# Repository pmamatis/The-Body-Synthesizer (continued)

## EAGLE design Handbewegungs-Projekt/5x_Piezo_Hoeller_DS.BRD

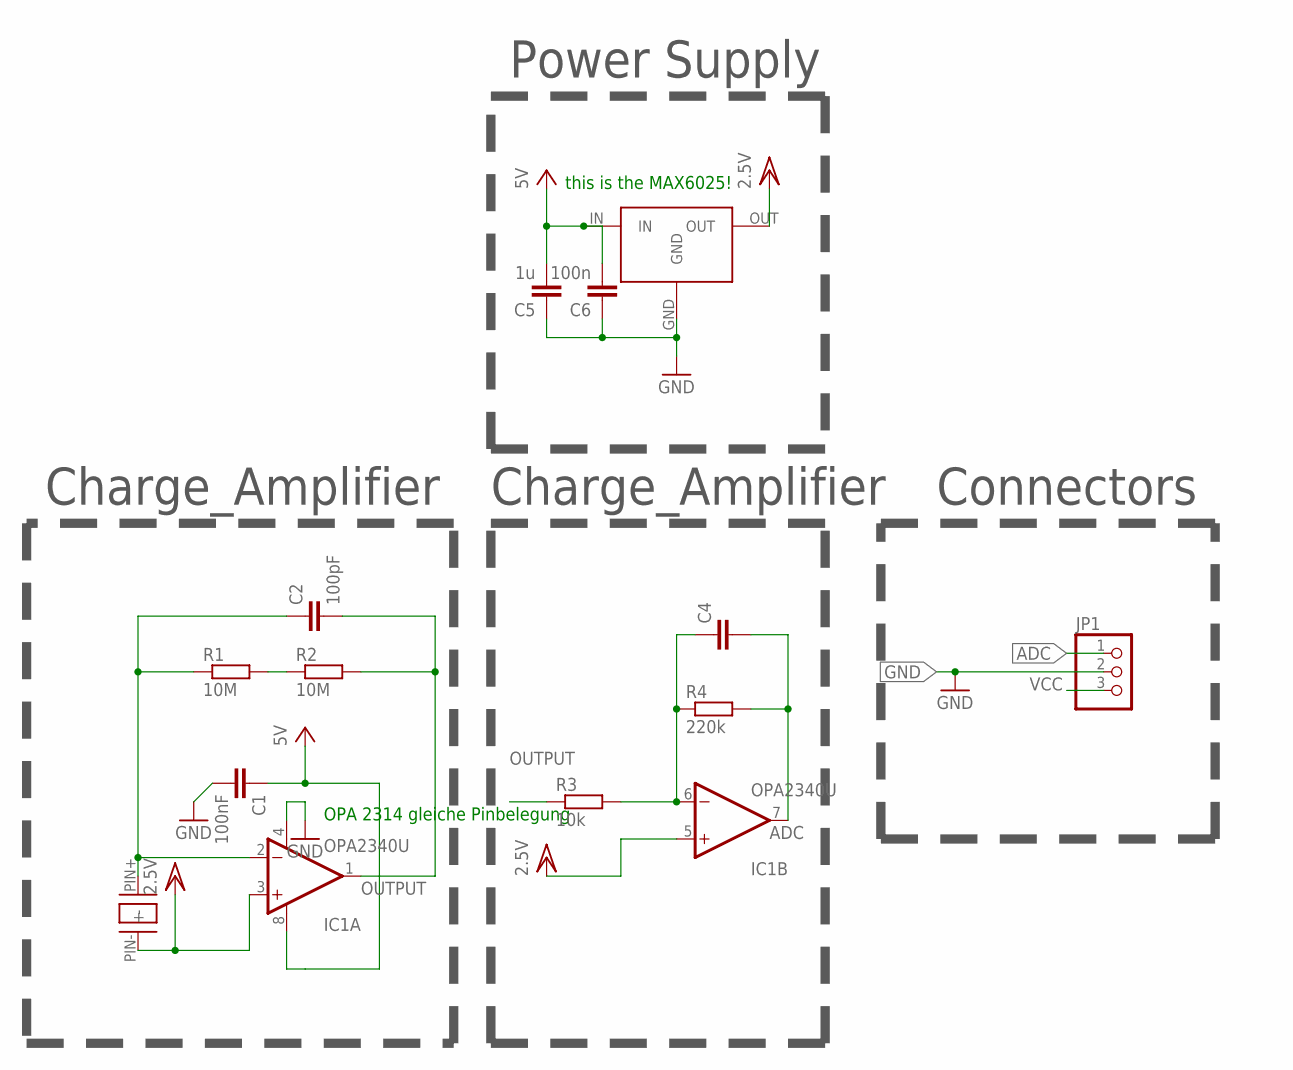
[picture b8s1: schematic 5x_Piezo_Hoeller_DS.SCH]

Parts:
C1: 100nF; C0603
C2: 100pF; C0603
C4: C-EUC0603; C0603
C5: 1u; C0603
C6: 100n; C0603
IC1: OPA2340U; SO08
JP1: PINHD-1X3; 1X03
R1, R2: 10M; R0603
R3: 10k; R0603
R4: 220k; R0603
U$1: MAX6018X; SOT-3
U$2: 10MMSCHEIBE; 10MM_SCHEIBE

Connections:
ADC: C4.2, IC1.7 (OUT), JP1.1, R4.2
GND: C1.2, C5.1, C6.1, IC1.4 (V-), JP1.2, U$1.GND
unnamed: C2.1, IC1.2 (-IN), R1.1, U$2.PIN+ (+)
unnamed: R1.2, R2.1
unnamed: C4.1, IC1.6 (-IN), R3.2, R4.1
OUTPUT: C2.2, IC1.1 (OUT), R2.2, R3.1
VCC: C1.1, C5.2, C6.2, IC1.8 (V+), JP1.3, U$1.IN
VCC/2: IC1.3 (+IN), IC1.5 (+IN), U$1.OUT, U$2.PIN- (-)

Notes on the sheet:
Power Supply
Charge_Amplifier
Connectors
OPA 2314 gleiche Pinbelegung
this is the MAX6025!

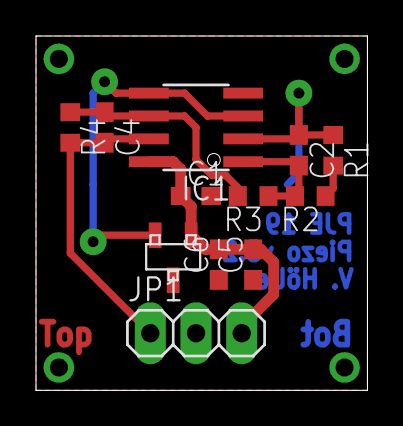
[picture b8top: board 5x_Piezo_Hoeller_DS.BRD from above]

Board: 2 copper layers, 18.4 x 19.7 mm, 13 parts (1 on the bottom side), 8 nets.

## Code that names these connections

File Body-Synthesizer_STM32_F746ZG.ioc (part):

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Mcu.Name=STM32F746ZGTx
Mcu.Package=LQFP144
Mcu.UserName=STM32F746ZGTx
PA0/WKUP.GPIOParameters=GPIO_Label
PA0/WKUP.GPIO_Label=DISP_DC
PA0/WKUP.Signal=GPIO_Output
PA2.Signal=USART2_TX
PA4.Signal=COMP_DAC1_group
PA5.Signal=COMP_DAC2_group
PA6.GPIOParameters=GPIO_Label
PA6.GPIO_Label=VRx
PA6.Signal=ADCx_IN6
PB0.GPIOParameters=GPIO_Label
PB0.GPIO_Label=VRy
PB0.Signal=ADCx_IN8
PB1.GPIOParameters=GPIO_Label
PB1.GPIO_Label=DISP_BUSY
PB1.Signal=GPIO_Input
PB14.GPIOParameters=GPIO_Label
PB14.GPIO_Label=Red_User_LED
PB14.Signal=GPIO_Output
PB2.GPIOParameters=GPIO_Label
PB2.GPIO_Label=SD_DI_MOSI
PB2.Mode=Full_Duplex_Master
PB2.Signal=SPI3_MOSI
PB3.GPIOParameters=GPIO_Label
PB3.GPIO_Label=DISP_CLK
PB3.Mode=Full_Duplex_Master
PB3.Signal=SPI1_SCK
PB4.Mode=Full_Duplex_Master
PB4.Signal=SPI1_MISO
PB5.GPIOParameters=GPIO_Label
PB5.GPIO_Label=DISP_DIN
PB5.Mode=Full_Duplex_Master
PB5.Signal=SPI1_MOSI
PB7.GPIOParameters=GPIO_Label
PB7.GPIO_Label=Blue_User_LED
PB7.Signal=GPIO_Output
PC0.GPIOParameters=GPIO_Label
PC0.GPIO_Label=Poti
PC0.Signal=ADCx_IN10
PC10.GPIOParameters=GPIO_Label
PC10.GPIO_Label=SD_CLK
PC10.Mode=Full_Duplex_Master
PC10.Signal=SPI3_SCK
PC11.GPIOParameters=GPIO_Label
PC11.GPIO_Label=SD_DO_MISO
PC11.Mode=Full_Duplex_Master
PC11.Signal=SPI3_MISO
PC13.GPIOParameters=GPIO_Label
PC13.GPIO_Label=ENTER_USER
PC13.Signal=GPXTI13
PC2.GPIOParameters=GPIO_Label
PC2.GPIO_Label=KEYBOARD_ADC
PC2.Signal=ADCx_IN12
PC3.Signal=ADCx_IN13
PC8.GPIOParameters=GPIO_Label,GPIO_ModeDefaultOutputPP
PC8.GPIO_Label=DISP_CS
PC8.GPIO_ModeDefaultOutputPP=GPIO_MODE_OUTPUT_PP
PC8.Signal=GPIO_Output
PC9.GPIOParameters=GPIO_Label
PC9.GPIO_Label=BACK
PC9.Signal=GPXTI9
PD6.Signal=USART2_RX
PD8.Mode=Asynchronous
PD8.Signal=USART3_TX
PD9.Mode=Asynchronous
PD9.Signal=USART3_RX
PE2.GPIOParameters=GPIO_Label
PE2.GPIO_Label=F4_SPI_CLK
PE2.Mode=Full_Duplex_Master
PE2.Signal=SPI4_SCK
PE5.GPIOParameters=GPIO_Label
PE5.GPIO_Label=F4_SPI_MISO
PE5.Mode=Full_Duplex_Master
PE5.Signal=SPI4_MISO
PE6.GPIOParameters=GPIO_Label
PE6.GPIO_Label=F4_SPI_MOSI
PE6.Mode=Full_Duplex_Master
PE6.Signal=SPI4_MOSI
PE8.GPIOParameters=GPIO_Label
PE8.GPIO_Label=ENTER
PE8.Signal=GPXTI8
PF0.GPIOParameters=GPIO_Label
PF0.GPIO_Label=GYRO_I2C_SDA
PF0.Mode=I2C
PF0.Signal=I2C2_SDA
PF1.GPIOParameters=GPIO_Label
PF1.GPIO_Label=GYRO_I2C_SCL
PF1.Mode=I2C
PF1.Signal=I2C2_SCL
PF10.GPIOParameters=GPIO_Label
PF10.GPIO_Label=SD_CS
PF10.Signal=GPIO_Output
PF12.GPIOParameters=GPIO_Label
PF12.GPIO_Label=DISP_RST
PF12.Signal=GPIO_Output
PF3.Mode=IN9
PF3.Signal=ADC3_IN9
PF5.Mode=IN15
PF5.Signal=ADC3_IN15
PF6.GPIOParameters=GPIO_Label
PF6.GPIO_Label=ADC_EMG_DC
PF6.Mode=IN4
PF6.Signal=ADC3_IN4
PF7.GPIOParameters=GPIO_Label
PF7.GPIO_Label=ADC_EMG_AC
PF7.Mode=IN5
PF7.Signal=ADC3_IN5
PG0.GPIOParameters=GPIO_Label,GPIO_ModeDefaultEXTI
PG0.GPIO_Label=SW
PG0.GPIO_ModeDefaultEXTI=GPIO_MODE_IT_FALLING
PG0.Signal=GPXTI0
PH0/OSC_IN.Mode=HSE-External-Oscillator
PH0/OSC_IN.Signal=RCC_OSC_IN
PH1/OSC_OUT.Mode=HSE-External-Oscillator
PH1/OSC_OUT.Signal=RCC_OSC_OUT
RCC.HSE_VALUE=8000000
RCC.SYSCLKFreq_VALUE=216000000
RCC.SYSCLKSource=RCC_SYSCLKSOURCE_PLLCLK
board=custom

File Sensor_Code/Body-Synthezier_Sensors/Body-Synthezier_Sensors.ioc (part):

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Mcu.Name=STM32F446R(C-E)Tx
Mcu.Package=LQFP64
Mcu.UserName=STM32F446RETx
PA10.GPIOParameters=GPIO_Label
PA10.GPIO_Label=LED_STRONG_TILT_BACK
PA10.Signal=GPIO_Output
PA13.GPIOParameters=GPIO_Label
PA13.GPIO_Label=TMS
PA13.Signal=SYS_JTMS-SWDIO
PA14.GPIOParameters=GPIO_Label
PA14.GPIO_Label=TCK
PA14.Signal=SYS_JTCK-SWCLK
PA2.GPIOParameters=GPIO_Label
PA2.GPIO_Label=USART_TX
PA2.Mode=Asynchronous
PA2.Signal=USART2_TX
PA3.GPIOParameters=GPIO_Label
PA3.GPIO_Label=USART_RX
PA3.Mode=Asynchronous
PA3.Signal=USART2_RX
PA5.Mode=Full_Duplex_Slave
PA5.Signal=SPI1_SCK
PA6.Mode=Full_Duplex_Slave
PA6.Signal=SPI1_MISO
PA7.Mode=Full_Duplex_Slave
PA7.Signal=SPI1_MOSI
PA8.GPIOParameters=GPIO_Label
PA8.GPIO_Label=LED_TILT_FRONT
PA8.Signal=GPIO_Output
PB10.GPIOParameters=GPIO_Label
PB10.GPIO_Label=LED_STRONG_TILT_FRONT
PB10.Signal=GPIO_Output
PB13.GPIOParameters=GPIO_Label
PB13.GPIO_Label=LED_STRONG_TILT_RIGHT
PB13.Signal=GPIO_Output
PB14.GPIOParameters=GPIO_Label
PB14.GPIO_Label=LED_CALIBRATED
PB14.Signal=GPIO_Output
PB3.GPIOParameters=GPIO_Label
PB3.GPIO_Label=LED_TILT_BACK
PB3.Signal=GPIO_Output
PB4.GPIOParameters=GPIO_Label
PB4.GPIO_Label=LED_STRONG_TILT_LEFT
PB4.Signal=GPIO_Output
PB5.GPIOParameters=GPIO_Label
PB5.GPIO_Label=LED_TILT_LEFT
PB5.Signal=GPIO_Output
PB8.Mode=I2C
PB8.Signal=I2C1_SCL
PB9.Mode=I2C
PB9.Signal=I2C1_SDA
PC13.GPIOParameters=GPIO_Label,GPIO_ModeDefaultEXTI
PC13.GPIO_Label=B1 [Blue PushButton]
PC13.GPIO_ModeDefaultEXTI=GPIO_MODE_IT_FALLING
PC13.Signal=GPXTI13
PC14-OSC32_IN.Signal=RCC_OSC32_IN
PC15-OSC32_OUT.Signal=RCC_OSC32_OUT
PC4.GPIOParameters=GPIO_Label
PC4.GPIO_Label=LED_TILT_RIGHT
PC4.Signal=GPIO_Output
PC9.GPIOParameters=GPIO_Label
PC9.GPIO_Label=MPU6050_Power
PC9.Signal=GPIO_Output
PH0-OSC_IN.Signal=RCC_OSC_IN
PH1-OSC_OUT.Signal=RCC_OSC_OUT
RCC.HSE_VALUE=8000000
RCC.SYSCLKFreq_VALUE=84000000
RCC.SYSCLKSource=RCC_SYSCLKSOURCE_PLLCLK
board=NUCLEO-F446RE
boardIOC=true

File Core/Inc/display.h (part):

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} y_row_value;

typedef enum {
	STEP1 = 40,
	STEP2 = 60,
	STEP3 = 80,
	STEP4 = 100,
	STEP5 = 120,
	STEP6 = 140,
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
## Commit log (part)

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2020-06-24 all_sines_LUT.m added
2020-06-24 cosmetics
2020-06-24 1.4 in progress
2020-06-24 dlmwrite
2020-06-30 LUT code writer 1.0
2020-06-30 sinLLUT
2020-07-02 verbessert
    LFO geht nicht
2020-07-07 BLOCKSIZE = 24k, wegen RAM speicher
    LUT und LFO im Flash gespeichert
2020-07-07 LFO calculate verbessert
    LUT und LFo in Flash schreiben hinzugefügt
2020-07-08 LFO Periode/4
2020-07-08 Samplerate = 96k
2020-07-08 Picture added
2020-07-30 Signal Syntrhesis 1.4 works first atempt, no bugs found but also not searched
2020-08-04 Signalsyntheses, möglicherweise fertig?!
2020-08-06 dynamische Voice Lautstärke
2020-08-12 changed LFO precision from 2 to 5
2020-08-12 LFO ready to use
2020-08-12 filters merged with new signal synthesis, LP test successful
2020-09-28 less RAM usage
    calculate_vector isnow directly given to the DAC, without having the output_vector
2020-09-30 Tremolo works, but still have to clean up!
2020-09-30 Tremolo is implemented!
2021-01-21 organized the code for the distortion-effect
2021-03-04 Add new directory by wiselom
2021-04-25 EMG board updates
2021-04-25 BSB.graphml added
2021-04-25 Lowpass filter working still! Next up: try band/highpass
2021-05-02 added Together Branch, merged tremolo and filters
2021-05-07 debug session
2021-05-07 debug session gelöst
2021-05-07 nichts hat sich veränder "nochmal pushen"
2021-05-14 merging begins
2021-05-14 Master -Branch First Commit
    This Branch must contain only working states of the Software. Use this Branch to develop and then merge back if everything is functional
2021-05-16 Parallel processing implemented: works for 1 band already, next up: Test all bands at the same time
2021-05-16 All bands tested at the same time with several test tones, worked! Next up: have a look to amplitude levels (e.g. testing filters with white noise)
2021-05-19 define aquidistance and atan_LUT_y in distortion-files instead of main-files
2021-05-21 added soft clipping based on exponential function;
    added CMSIS-DSP and CMSIS-Core-Library
2021-05-21 EQ Bandpass debugged, Band 1 & 2 working properly - Next up: Test Band 3 - 5
2021-05-23 Individual Bandpass filters implemented, center frequencies have to be specified
2021-05-23 started with the new structure, which should be implemented
2021-05-25 now it is possible to turn Voice1 Off and On again
2021-05-26 Switching between Voices, ADSR, EQ, Distortion and Tremolo possible
2021-05-27 Code angepasst
2021-06-01 Keyboard slightly edited (2 drills) for manufacturing
2021-06-01 ADC reads AC (in12) and DC (in13) channel of emg
2021-06-02 All types of filter implemented, next up: test new ones with poti (change cutoff, Q, Gain)
2021-06-02 Warnings solved, now Signal_Syntheis Errors occured >> Will be fixed by Paul and Marc
2021-06-02 Keyboard panelized
2021-06-02 emg adc ready to use
2021-06-06 ADC1 Channel 13 read in for poti value while signal synthesis as well as printing via uart is working
2021-06-06 Debugging necessary
2021-06-07 Tremolo does not work in combination with display; permanent calculation of LFO could be the problem
2021-06-08 Voice, Distortion and Tremolo work together; had to remove effects_process and put function calls into signal_synthesis
2021-06-11 HS / LS tested successfully with changing Gain & Cutoff in Filters_Reinit() - next up: PEQ
2021-06-11 PEQ Att. Problem solved by introducing Notch filter >> Complete EQ works now!
2021-06-13 Mainboard created
2021-06-13 pinbelegung für display geändert (SPI)
2021-06-18 changed CLK and MOSI from SPI6 to SPI1 for the display
2021-06-18 changed Button_Back and DISP_CS pins
2021-06-21 Pinout test done, SD card works in this setup!
2021-06-21 update rotation of the display
2021-06-22 integrated keyboardmode on/off, bu adsr reacts too slow. processing has to be done at different place
2021-06-22 Auf dem stand von Keyboard-Branch, ADSR weißt dennoch Fehler auf
2021-06-24 Optimized for speed, keyboard can be played now
2021-06-25 ADSR works in combination with the display! Now its possible to switch between keyboard- and synthesizemode and play with the parameters
2021-06-27 soft clipping added, but amplitude does change when gain is increased
2021-06-28 Bemaßung hinzugefügt
2021-07-10 Mainboard updated II
2021-07-15 Mainboard updated IV
2021-07-18 Mainboard updated VI (ready2route)
2021-07-18 Mainboard updated VIII: routed completely, only need to check SD Card size
2021-07-20 Production data for ordering Mainboard, Keys, UI and EQ at JLCPCB
2021-07-21 Production data changed
2021-07-22 Display-Update stört Signale nicht mehr so stark, da nun seltener geupdated wird
2021-08-12 Namen zurechtgerückt
2021-08-12 Display structure changed
2021-08-13 new basic structure implemented
2021-08-13 EQ BOM updated
2021-08-15 BOM updated
2021-08-15 added input_interfaces files
2021-08-19 deleted HAL_ADC_Start_DMA(&hadc1, &Display.ADC1input, 1); in main.c file
2021-08-23 added Interface Controll
2021-08-23 p_Equalizer_Settings implemented and now ready to merge with p_Equalizer_Overview
2021-08-23 p_Equalizer_overview and p_Equalizer_Settings combined
2021-08-24 cleaned up code
2021-08-24 Voices page is working
2021-08-25 Peak detection implemented, not properly working with LED
2021-08-31 EKG Recognition working!!!
2021-09-02 Added pictures for EMG and Mainboard for final report
2021-09-03 display structure is running correctly, but filter page is buggy, when filter is turned on
2021-09-03 drum computer works! now lookup tables have to be read in via sd card
2021-09-03 fixed some display-bugs and dummy structure has to be implemented
2021-09-04 Single Output already possible
2021-09-04 Drumsaples added, reading from SD card works, only need to find a solution for puting LUTs into FLASH and not RAM
2021-09-05 Tried to stream samplewise from SD Card, implicit Bug because of missing header?
2021-09-09 Drum_Computer now working with 4 Samples at a time, loading them from SD card into RAM. Drumsamples are sampled down by 4
2021-09-09 Poti & Filters included to have a lowshelf filter on drums with settable cutoff
2021-09-10 Test
2021-09-10 invert/toggle DrumMatrix entrys in GPIO external interrupt Callback; next filled rectangle should be set/reset
2021-09-10 LFO uncommented
2021-09-10 Drums working together with NewSignal and partly with Filtercutoff reinit. SR: 48kHz, sinLUTs and wavLUTs adapted via matlab scripts. Next up: Trying bigger blocksizes or even lower SR?
2021-09-10 48 kHz change
2021-09-10 9 voices + 4 drums + eq + tremolo + distortion
2021-09-10 Fettes Noise (nun normalized) + Filter + Drums
2021-09-10 24kHz change - drums working nicely
2021-09-11 New drumkit plus updated matlab file, need to go on there
2021-09-11 Rock loud drumkit added
2021-09-11 Tremolo cleaned, WahWah already created, need to finish it
2021-09-11 cosmetics, LFO_FMIN adapted to new low Hz LUTs
2021-09-11 Lowest frequency bug and wrong number of frequencies fixed
2021-09-11 naice ambient lfo wah with poti for future live set
2021-09-11 Noise tested with WahWah, reinitialisation update rate decreased due to high calculation intensity of noise and filter reinit
2021-09-12 drum matrix pattern is displayed whenever you switch into the p_Drumcomputer_Settings function
2021-09-13 Sequencer framwork working for one note to be played together with adsr and drums, keyboard flag changed, next up: add more possible notes
2021-09-13 Changed ADSR if bounderies as well as drumcomputer resetting drum_index to 0 but click bug still existing
2021-09-16 drum computer and sequencer now ready to merge into the display
2021-09-17 filterd with GYro working
2021-09-19 Backup Gyroskop_Paul
2021-09-23 drummachine merge, callback main.c still to do (Button), .ioc check
2021-09-24 added GPIO callback to main function
2021-09-25 added volume and presets function -> fuckup, when keyboard is played at the same time as drumcomputer/sequencer. Problem with IDs?
2021-09-26 mofified delete_effects
2021-09-26 wah wah and autowahwah implemented -> settings have to be implemented in the display
2021-09-28 keyboard is making problems
2021-09-30 successful detection of UP&DOWN and RIGHT&LEFT movements
2021-10-01 keyboard can be played with 3 simultaneous notes, adsr tail deleted by increasing keyboard SR, SetTimerSettings has to be TIM case sensitive, keyboard is cutting signal when played too fast
2021-10-02 Readded sound samples
2021-10-02 keyboard is completed
2021-10-02 all drum samples adjusted to start from sample 1 without delay
2021-10-02 fuckup, when preset is entered: limiting function still wrong
2021-10-03 tremolo- and wahwah- lfo rate bug fixed
2021-10-06 pushen an pauls b-day
2021-10-06 emg in process
2021-10-07 extended preset function
2021-10-13 "plöp"-sound in voices reduced by putting it into signal synthesis and II_Display_Voices
2021-10-13 fixed some display bug in wahwah, settings, but mid freq still plotted in overview page when autowahwah is used
2021-10-15 deleteSignal neu machen, plop am anfang über init gelöst?
2021-10-16 merged Paul and Elom <3
2021-10-17 improved tremolo rate change, but it is still making problems
2021-10-20 changed LFO_SingleValueProcess
2021-10-20 tried to change tremolo depth on each max. of a sine wave, but still some bugs in amp jumping
2021-10-22 tremolo and wahwah work without any amplitude fuckups;
    poti averaged to reduce influence of noise;
    display cosmetics with poti_moved etc.
2021-10-24 button interrupt preemtpion priority increased (from 1 to 0);
    currently loaded drumkit shown above name of samples
2021-10-27 noise generator implemented
2021-10-28 tremolo rate controllable via gyro/accelerometer
2021-11-04 all initialized parameters are set in the display;
    drumkit can be changed without a fuckup;
    button changed for drumkit from left to right button;
    BPM changes only after fourfour, but display is not updated immediately
2021-11-05 max. amplitude (volume) limited to 0.3
2021-11-05 Elom added, SR problem needs to be fixed
2021-11-11 drumfilter works, but the page has to be changed from the equalizer page to the drumcomputer page
2021-11-11 EMG page eingerichtet, aber die maximalen werte müssen noch durch probieren angepasst werden
2021-11-12 Preset 2 added
2021-11-12 drumfilter implemented
2021-11-17 distortion ready and merged
2021-11-19 currently implementing presets
2021-11-20 tremolo and wah wah-lfo frequency rate bug fixed
2021-11-21 Revert "changed ioc settings: timer 5 and timer 6 to timer 1 & irq priorities"
    This reverts commit 021bad5e3134a7439191309bfdfd77357e1c5b76.
    changeg display spi baud rate, extended wahwah_sources size, volume adjusted to lower values for testing, usart2 (former sd card test usart) deleted
2021-11-21 3 presets implemented
2021-11-21 ecg heartrate bpm control implemented, but not working yet
2021-11-23 Surprise commit
2021-11-26 ECG and EMG tested and parameters are integrated into the display page
2021-11-27 BPM updated in display while changed by ECG
2021-11-27 major, minor and freestyle scale modes work for Voices and hardcoded for gyro voices yet
2021-12-01 Major, Minor and Freestyle Scale implemented into sequencer - it works
2021-12-01 adjusted filter input interfaces to sweep faster while playing EQ with gyro and Filters_Reinit_Gyro function
2021-12-27 cleaned up code by removing unnecessary variables and comments
2022-01-05 Bereinigter Code um ihn an den Bericht anzuhängen
2022-01-06 header files kommentiert
2022-01-21 all files are commentet
2022-01-31 first Doku Version ready
2022-02-04 doxygen-Doku ergänzt
2022-02-04 kompelierbar
2022-02-07 cosmetics for report
2022-02-17 Drumcomputer / Sequencer graphmls added
2022-02-20 Sch bild
2022-02-20 keyboard brdV2 pic added
2022-02-20 Keyboard pictures added and sch updated
2022-02-22 Doxgen um Matlab erweitert
2022-02-22 Matlab works
2022-02-22 Revert ".gitignore update"
    This reverts commit 651362b3661256f62fe27b7781636f0aba2e56b7.
2022-02-22 Alles wieder im Lot commit :D
2022-02-22 updated Distortion_LUT.m
2022-03-02 DCS BSBs updated
2022-03-06 Filter plots extended
2022-03-29 Some briefs & correctures
2022-03-30 Neu Kompiliert
2022-03-31 Sensor_code update
